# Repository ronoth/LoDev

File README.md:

# LoDev
Hardware files and documentation for LoDev

## Specifications

* [S76S SoC documentation](S76S-product-specifications.pdf)
* [STM32L073 datasheet](https://www.st.com/resource/en/datasheet/stm32l073rz.pdf)

## Design Files

Checkout the eagle [.brd](lodev-s76s.brd) and [.sch](lodev-s76s.sch) files in this repository.  A [schematic pdf](lodev-s76s-sch.pdf) is also available.

## Pinout

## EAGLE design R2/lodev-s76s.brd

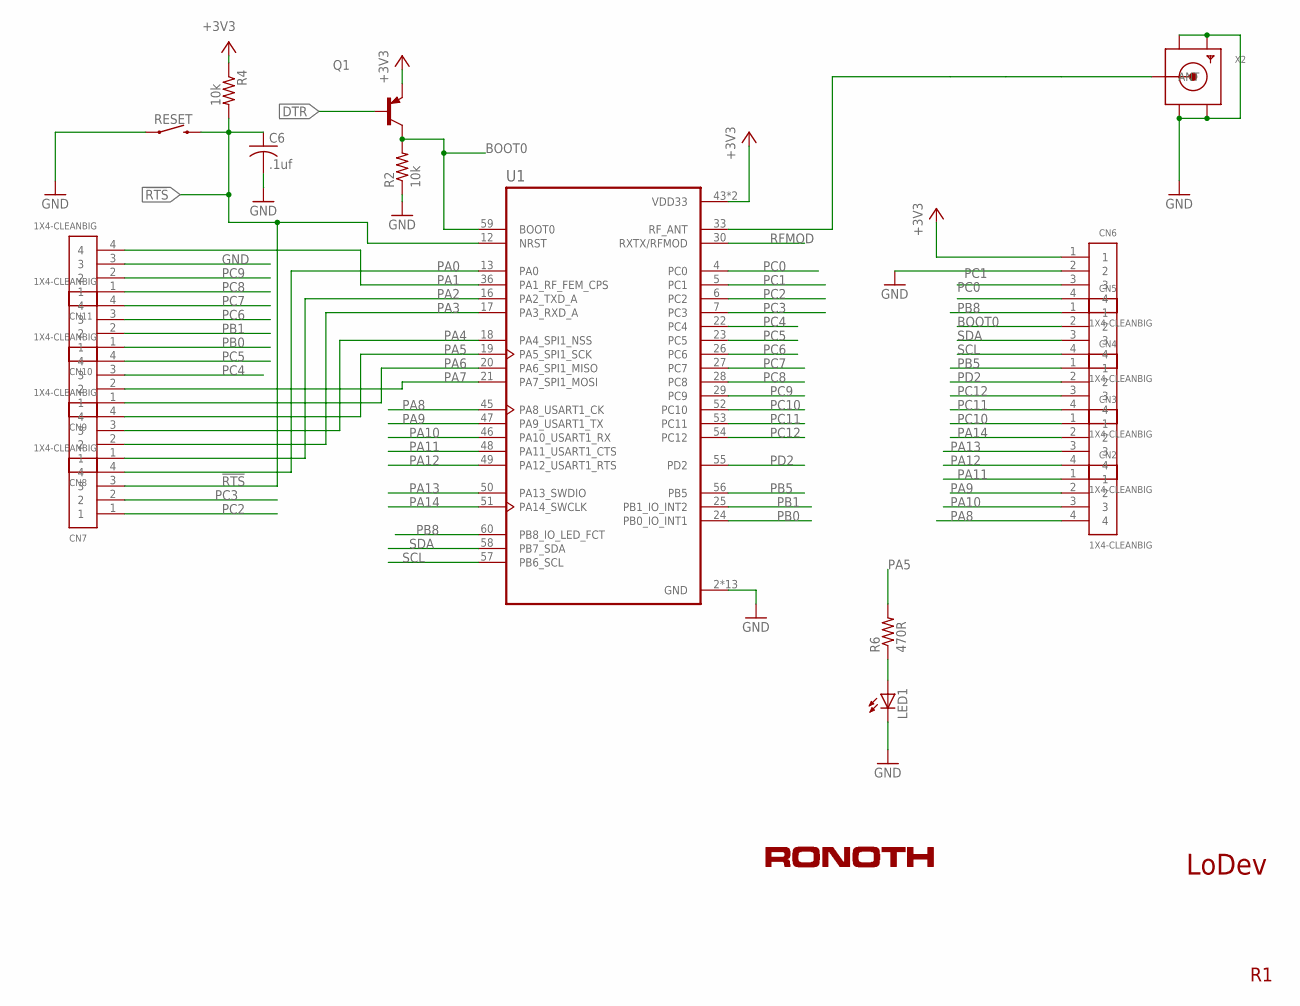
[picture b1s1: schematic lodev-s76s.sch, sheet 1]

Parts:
C6: .1uf; C0603K
CN2, CN3, CN4, CN5, CN6, CN7, CN8, CN9, CN10, CN11: 1X4-CLEANBIG; 1X04-CLEANBIG
LED1: LEDCHIPLED_0603; CHIPLED_0603
Q1: TRANSISTOR_BJT_PNP-SOT-23-BCE; SOT-23
R2, R4: 10k; R0603
R6: 470R; R0603
RESET: MOMENTARY-SWITCH-SPST-SMD-6.0X3.5MM; TACTILE_SWITCH_SMD_6.0X3.5MM
U1: S76S; ACSIP_S76S
X2: SMACONNECTOR_EDGE; SMA_EDGELAUNCH

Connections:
!RTS: C6.1, CN7.3, R4.2, RESET.2, U1.12 (NRST); also elsewhere on the board
+3V3: CN6.1, Q1.3 (E), R4.1, U1.43 (VDD33), U1.44 (VDD33); also elsewhere on the board
BOOT0: CN5.2, Q1.2 (C), R2.2, U1.59 (BOOT0)
DTR: Q1.1 (B); also elsewhere on the board
GND: C6.2, CN6.2, CN11.3, LED1.C, R2.1, RESET.1, U1.2 (GND), U1.3 (GND), U1.14 (GND), U1.15 (GND), U1.31 (GND), U1.32 (GND), U1.34 (GND), U1.35 (GND), U1.37 (GND), U1.39 (GND), U1.41 (GND), U1.61 (GND), U1.62 (GND), X2.GND@1 (GND4), X2.GND@2 (GND3), X2.GND@3 (GND2), X2.GND@4 (GND1); also elsewhere on the board
unnamed: U1.33 (RF_ANT), X2.P (ANT)
unnamed: LED1.A, R6.1
PA0: CN7.4, U1.13 (PA0)
PA1: CN11.4, U1.36 (PA1_RF_FEM_CPS)
PA2: CN8.1, U1.16 (PA2_TXD_A)
PA3: CN8.2, U1.17 (PA3_RXD_A)
PA4: CN8.3, U1.18 (PA4_SPI1_NSS)
PA5: CN8.4, R6.2, U1.19 (PA5_SPI1_SCK)
PA6: CN9.1, U1.20 (PA6_SPI1_MISO)
PA7: CN9.2, U1.21 (PA7_SPI1_MOSI)
PA8: CN2.4, U1.45 (PA8_USART1_CK)
PA9: CN2.2, U1.47 (PA9_USART1_TX); also elsewhere on the board
PA10: CN2.3, U1.46 (PA10_USART1_RX); also elsewhere on the board
PA11: CN2.1, U1.48 (PA11_USART1_CTS)
PA12: CN3.4, U1.49 (PA12_USART1_RTS)
PA13: CN3.3, U1.50 (PA13_SWDIO)
PA14: CN3.2, U1.51 (PA14_SWCLK)
PB0: CN10.1, U1.24 (PB0_IO_INT1)
PB1: CN10.2, U1.25 (PB1_IO_INT2)
PB5: CN4.1, U1.56 (PB5)
PB8: CN5.1, U1.60 (PB8_IO_LED_FCT)
PC0: CN6.4, U1.4 (PC0)
PC1: CN6.3, U1.5 (PC1)
PC2: CN7.1, U1.6 (PC2)
PC3: CN7.2, U1.7 (PC3)
PC4: CN9.3, U1.22 (PC4)
PC5: CN9.4, U1.23 (PC5)
PC6: CN10.3, U1.26 (PC6)
PC7: CN10.4, U1.27 (PC7)
PC8: CN11.1, U1.28 (PC8)
PC9: CN11.2, U1.29 (PC9)
PC10: CN3.1, U1.52 (PC10)
PC11: CN4.4, U1.53 (PC11)
PC12: CN4.3, U1.54 (PC12)
PD2: CN4.2, U1.55 (PD2)
RFMOD: U1.30 (RXTX/RFMOD)
SCL: CN5.4, U1.57 (PB6_SCL)
SDA: CN5.3, U1.58 (PB7_SDA)

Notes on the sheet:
LoDev

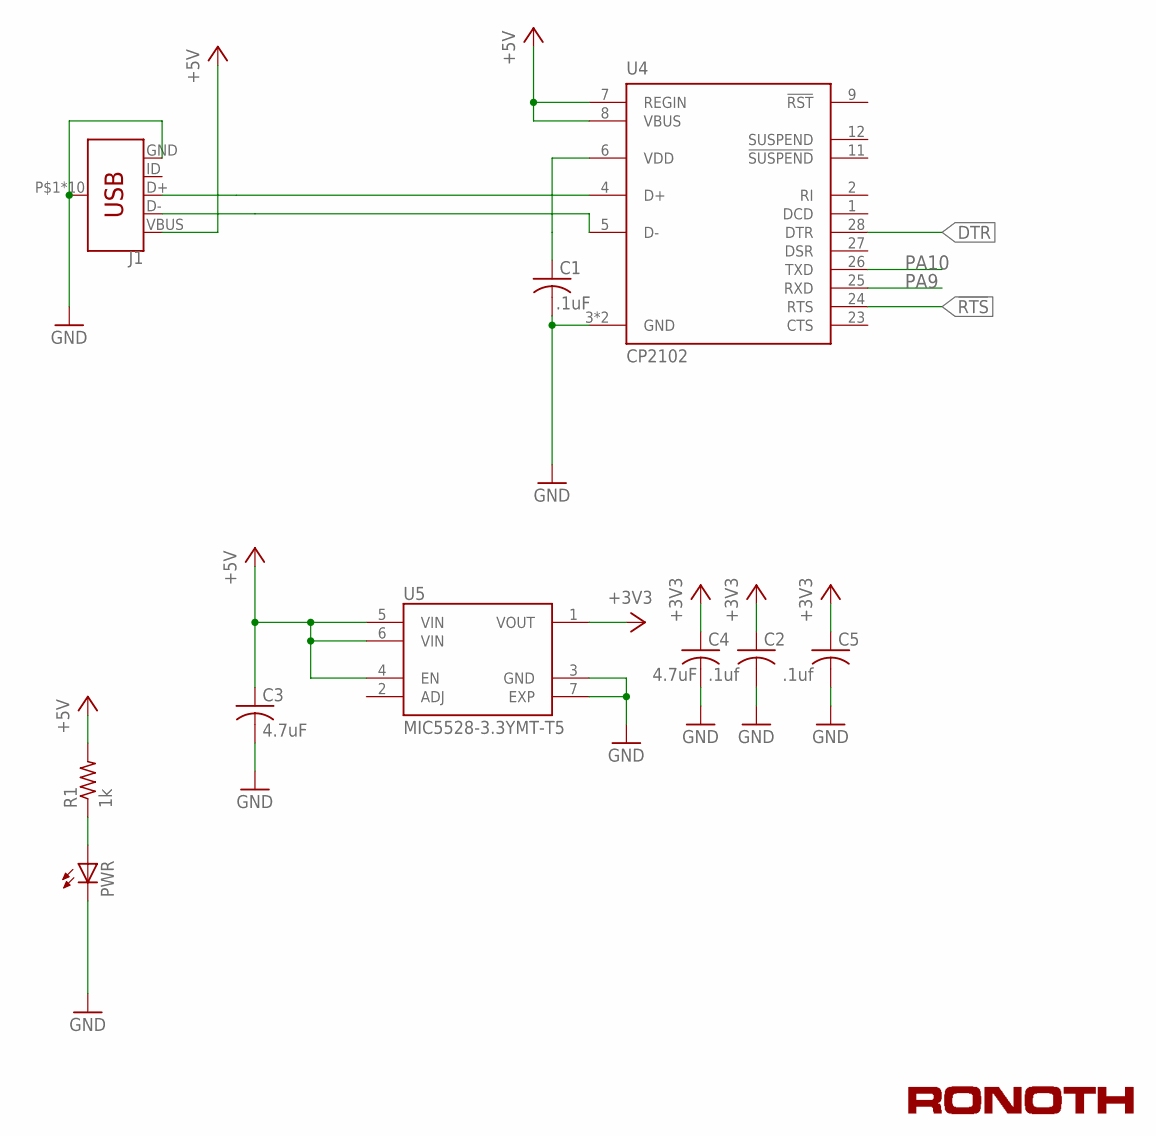
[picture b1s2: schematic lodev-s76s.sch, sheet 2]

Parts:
C1: .1uF; C0603K
C2, C5: .1uf; C0603K
C3, C4: 4.7uF; C0603K
J1: USB_MICRO-B; USB-MICROB-PTH
PWR: LEDCHIPLED_0603; CHIPLED_0603
R1: 1k; R0603
U4: CP2102; MLP28
U5: MIC5528-3.3YMT-T5; SON50P160X160X60-7N

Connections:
!RTS: U4.24 (RTS); also elsewhere on the board
+3V3: C2.1, C4.1, C5.1, U5.1 (VOUT); also elsewhere on the board
+5V: C3.1, J1.VBUS, R1.2, U4.7 (REGIN), U4.8 (VBUS), U5.4 (EN), U5.5 (VIN), U5.6 (VIN)
D+: J1.D+, U4.4 (D+)
D-: J1.D-, U4.5 (D-)
DTR: U4.28 (DTR); also elsewhere on the board
GND: C1.2, C2.2, C3.2, C4.2, C5.2, J1.GND, J1.P$1 (SHIELD), J1.P$3 (SHIELD), J1.P$4 (SHIELD), J1.P$8 (SHIELD), J1.P$10 (SHIELD), J1.P$12 (SHIELD), J1.SHEILD2 (SHIELD), J1.SHIELD, J1.SHIELD3 (SHIELD), J1.SHIELD4 (SHIELD), PWR.C, U4.3 (GND), U4.EXP (GND), U5.3 (GND), U5.7 (EXP); also elsewhere on the board
unnamed: PWR.A, R1.1
unnamed: C1.1, U4.6 (VDD)
PA9: U4.25 (RXD); also elsewhere on the board
PA10: U4.26 (TXD); also elsewhere on the board

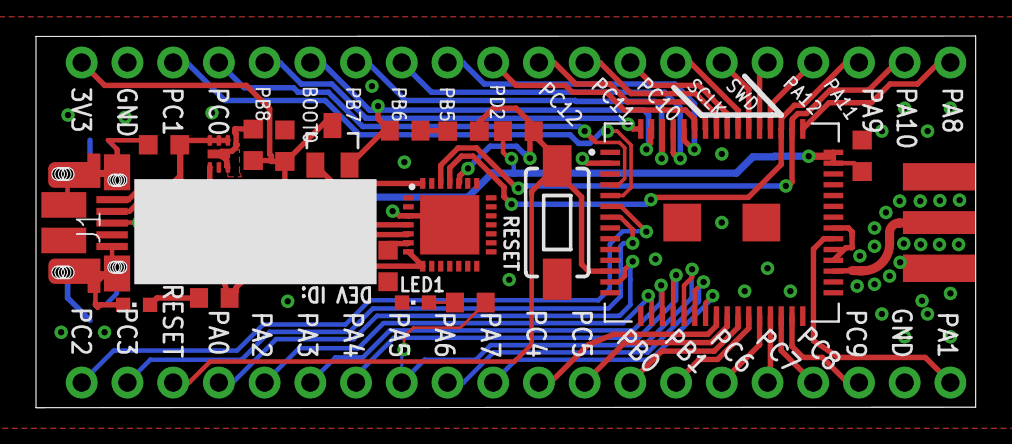
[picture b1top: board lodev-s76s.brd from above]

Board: 2 copper layers, 52.2 x 20.7 mm, 29 parts (0 on the bottom side), 47 nets.

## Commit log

2019-04-24 'initial'
2019-04-24 Add pinout docs and S76S specs
2019-12-20 R2 supports DFU over USB/UART

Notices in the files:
parts and their libraries:
SparkFun-Switches: Licensing: Creative Commons ShareAlike 4.0 International - https://creativecommons.org/licenses/by-sa/4.0
